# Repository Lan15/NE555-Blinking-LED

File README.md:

# NE555-Blinking-LED
Implementing blinking LED using IC NE555 by drawing ERC free schematic with required footprints and preparing the layout considering the constrains, mechanical aspects, routing thus finally making it ready for production by generating BOM (List of the mechanical parts) and Gerber files required by the manufacturer.

# Go through 
10_HW_v8\01_PCB\20_release\VersionList,
10_HW_v8\01_PCB\20_release\250402_NE555_Blinking_LED_001\10_work\00_Note,
10_HW_v8\01_PCB\20_release\250402_NE555_Blinking_LED_001\10_work\70_ReleaseNote\ReleaseNote,
10_HW_v8\01_PCB\20_release\250402_NE555_Blinking_LED_001\10_work\80_KiCad\note.

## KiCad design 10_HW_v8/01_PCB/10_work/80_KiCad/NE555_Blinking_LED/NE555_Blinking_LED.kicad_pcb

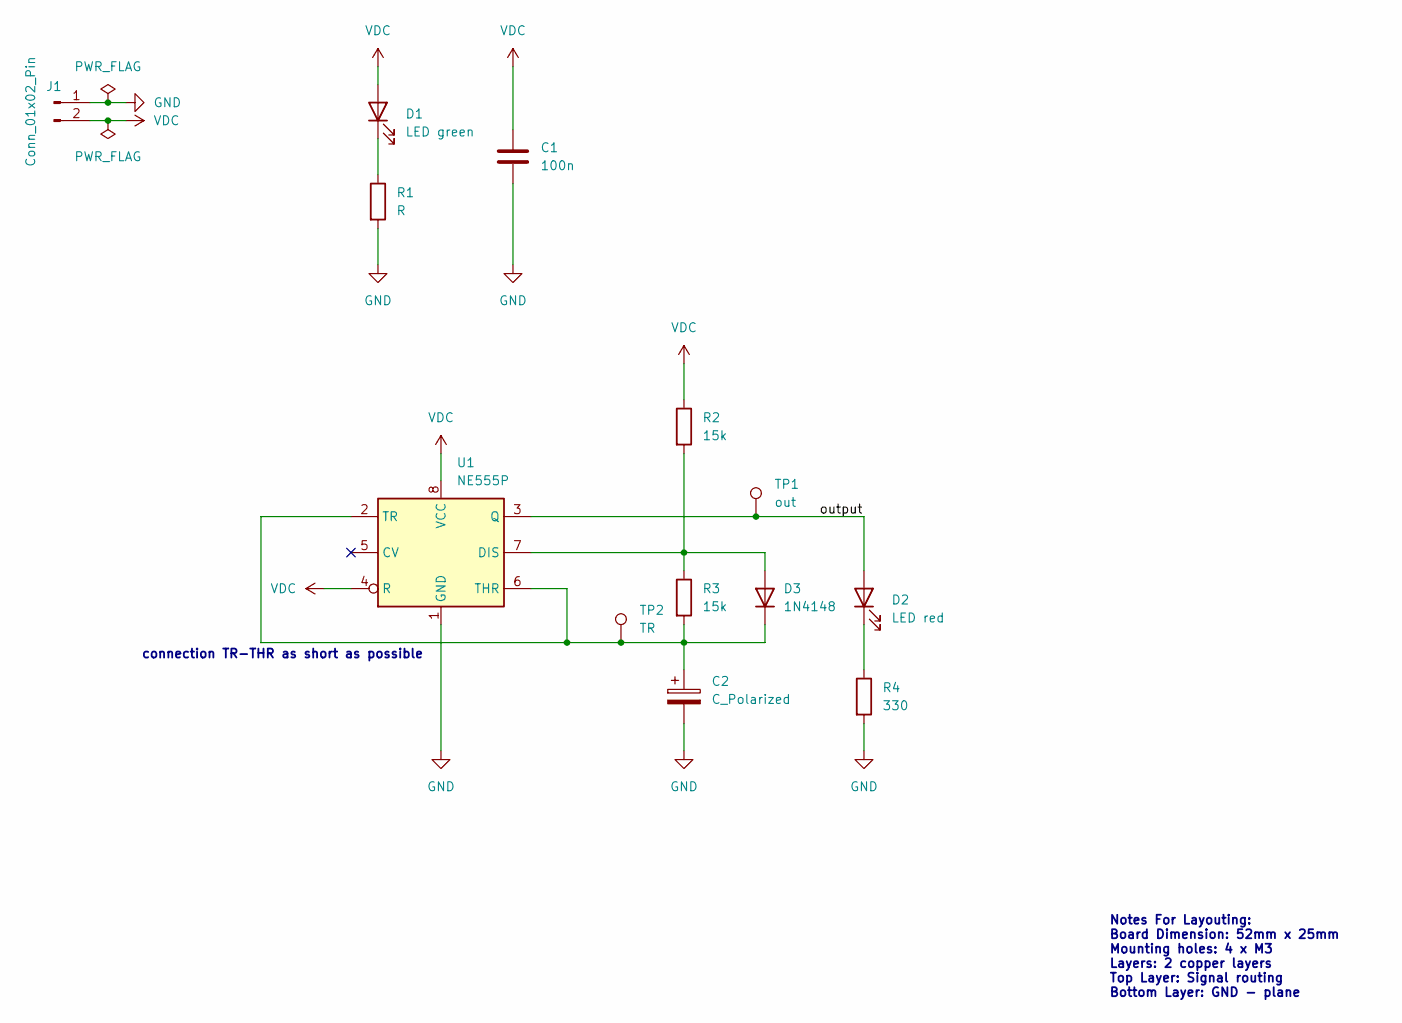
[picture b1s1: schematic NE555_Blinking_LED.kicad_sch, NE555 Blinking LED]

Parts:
C1: 100n; C_Rect_L7.2mm_W3.0mm_P5.00mm_FKS2_FKP2_MKS2_MKP2
C2: C_Polarized; CP_Radial_D10.0mm_P2.50mm
D1: LED green; LED_1206_3216Metric_Pad1.42x1.75mm_HandSolder
D2: LED red; LED_D5.0mm
D3: 1N4148; D_DO-35_SOD27_P7.62mm_Horizontal
J1: Conn_01x02_Pin; PinHeader_1x02_P2.54mm_Vertical
R1: R; R_1206_3216Metric_Pad1.30x1.75mm_HandSolder
R2, R3: 15k; R_Axial_DIN0207_L6.3mm_D2.5mm_P10.16mm_Horizontal
R4: 330; R_Axial_DIN0207_L6.3mm_D2.5mm_P10.16mm_Horizontal
TP1: out; PinHeader_1x01_P2.54mm_Vertical
TP2: TR; PinHeader_1x01_P2.54mm_Vertical
U1: NE555P; DIP-8_W7.62mm

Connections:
/output: D2.2 (A), TP1.1, U1.3 (Q)
GND: C1.2, C2.2, J1.1, R1.2, R4.2, U1.1 (GND)
unnamed: D1.1 (K), R1.1
unnamed: D2.1 (K), R4.1
unnamed: D3.2 (A), R2.2, R3.1, U1.7 (DIS)
unnamed: C2.1, D3.1 (K), R3.2, TP2.1, U1.2 (TR), U1.6 (THR)
VDC: C1.1, D1.2 (A), J1.2, R2.1, U1.4 (R), U1.8 (VCC)

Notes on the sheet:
Notes For Layouting: Board Dimension: 52mm x 25mm Mounting holes: 4 x M3 Layers: 2 copper layers Top Layer: Signal routing Bottom Layer: GND - plane
connection TR-THR as short as possible

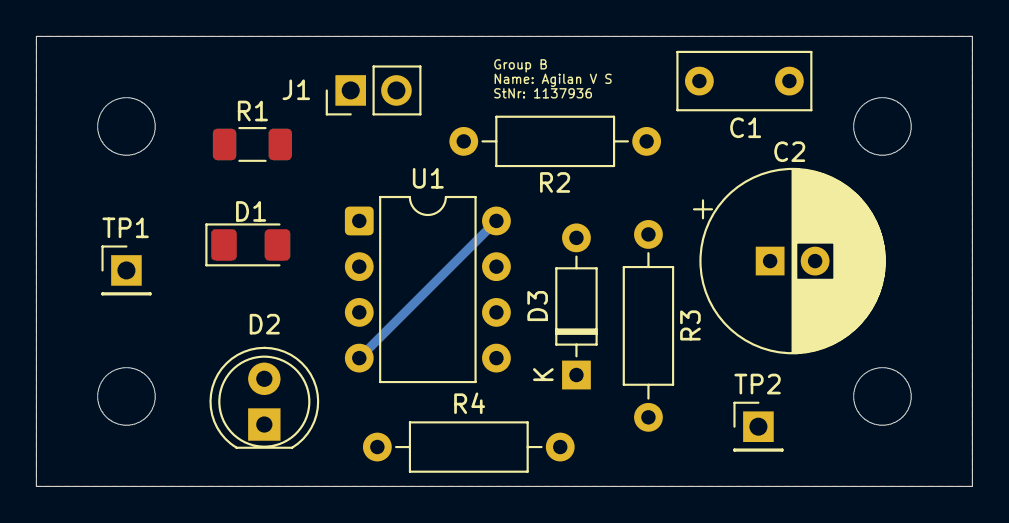
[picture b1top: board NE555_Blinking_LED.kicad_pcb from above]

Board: 2 copper layers, 52.0 x 25.0 mm, 13 parts (0 on the bottom side), 7 nets.

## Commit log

2025-04-15 Update README.md
    Updated here the project version control documents details .
